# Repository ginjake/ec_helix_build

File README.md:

## LICENSE
creative commons non commercial

商用利用したい場合は twitter @sirojake にご相談ください  
please contact me for commercial use.
## developer 
ginjake

## 静電容量Helixとは？
Helix Keyboardの基板を差し替え、静電容量スイッチに対応させる為の基板です   
Varmiloスイッチ用とラバードーム用の2種類があり、別々の基板になっています。

## 外部の使用ライブラリ
### シンボルライブラリー
phi-kbd-library-master https://github.com/zk-phi/phi-kbd-library  
kbd https://github.com/foostan/kbd  

### フットプリントライブラリー
kbd https://github.com/foostan/kbd  
phi-kbd-library-master https://github.com/zk-phi/phi-kbd-library  
rd https://github.com/KiCad/kicad-footprints/tree/master/Resistor_SMD.pretty  
cs　https://github.com/KiCad/kicad-footprints/tree/master/Capacitor_SMD.pretty  

# 組み立て方 
本家Helixとの共通部分については省略しています。  
Varmilo版とラバードームで共通箇所が多いため、まとめて記載しています。

こちらのビルドログも参考になるので、目を通しておくと良いかもしれません  
https://orumin.blogspot.com/2020/10/helix-ec-helix-niz-ver.html

## 注意
本キットは組み立て難易度が高く、使うパーツも特殊です。  
自作キーボード初心者の方にはおすすめしません。  
通常のメカニカルスイッチでは動作せず、特殊なスイッチが必要になります。

# Varmiloスイッチについて
Varmilo社が出しているスイッチで、静電容量メカニカルとも呼ばれています。  
単体では販売されていないので、既製品を分解して入手する必要があります。  
ふもっふのお店のカスタムキーボードサービスで
デイジー軸 桜軸 ローズ軸などを選択して発注するのが一番手軽です。
https://jp.varmilo.com/keyboardproscenium/

# ラバードームスイッチについて
HHKBやREAL FORCE、NiZで採用されている方式です。  
トップハウジング、ステム、ラバードーム、コニックリングで構成されており、  
NiZキーボードを購入して分解することで全て手に入れることが出来ます。

## 部品

下記は両手分を作るのに必要なパーツ数です  

### 本家 Varmilo ラバードーム共通部品
| 名前 | 数 | 備考 |
| ---- | ---- | --- |
| Pro Micro | 2個 | |
| TRRSジャック | 2個 | |
| タクトスイッチ | 2個 | |
| スプリングピンヘッダ 12P | 4個 | コンスルーとも呼ばれています |
| プレート | 2セット| 遊舎工房の切り出しサービスがおすすめです|
| OLED保護プレート | 2枚 | |
| ゴム足 | 12個 |  |
| キーキャップ | 64個 | CherryMX軸 |
| 3.5mmオーディオケーブル | 左右合わせて1本 | 左右のキーボード接続用 |
| micro USBケーブル | 左右あわせて1本 | 
| OLEDモジュール | 2個 | OLED用（オプション） |
| ピンソケット 4P | 2個 | OLED用（オプション） |
| ピンヘッダ 4P | 2個 | OLED用（オプション） |
| M2スペーサー 8mm | 4個 | (OLED用)|
| sk6812mini| varmilo版 64個,ラバードーム版 54個  | LEDを付ける場合のみ|

### ラバードーム版追加部品
| 名前 | 数 | 備考 |
| ---- | ---- | --- |
| M5スペーサー | 8個 | |
| M2用ワッシャ | 8個(適宜) | |
| M2スペーサー 7mm| 8個 | |
| M2ネジ 4mm| 16個 | (低頭のほうが望ましい)|
| M2ネジ 6mm| 8個 | (低頭のほうが望ましい)|

### 本家と異なる部品
| 名前 | 数 | 備考 | 入手先 |
| ---- | ---- | --- | ---- |
| PCB | 2枚 | | |
| 静電容量キースイッチ | 64個 | 詳しくは後述します | |
| スイッチソケット | 64個 | varmilo版のみ https://yushakobo.jp/shop/a01ps/ | |
| 1608(0603)チップ抵抗 100K | 14 | | https://www.sengoku.co.jp/mod/sgk_cart/detail.php?code=EEHD-57HD |
| 1608(0603)チップ抵抗 10K | 4 | | https://www.sengoku.co.jp/mod/sgk_cart/detail.php?code=EEHD-57GX |
| 1608(0603)チップ抵抗 1KΩ | 4| | https://www.sengoku.co.jp/mod/sgk_cart/detail.php?code=EEHD-57GK |
| 1608(0603)チップ抵抗 200Ω | 12 | | https://www.sengoku.co.jp/mod/sgk_cart/detail.php?code=EEHD-57FZ |
| 1608(0603)チップ抵抗 51KΩ | 2 | | https://www.sengoku.co.jp/mod/sgk_cart/detail.php?code=EEHD-57H7 |
| 1608チップ積層セラミックコンデンサー 50Vdc 220pF | 2 | GRM1882C1H221JA01D*A (10個入り)| https://www.marutsu.co.jp/GoodsDetail.jsp?salesGoodsCode=19297&shopNo=3 |
|チップトランジスタ　2SC2712-GR 50V150m | 2 | | http://akizukidenshi.com/catalog/g/gI-00761/ |
| 74HC4051DB IC MUX/DEMUX 8X1 16SSOP | 2 | | https://www.marutsu.co.jp/pc/i/24340308/ |
| 2回路入オペアンプAD8616ARM | 2 | | http://akizukidenshi.com/catalog/g/gI-04570/ |
| ジャンパ用の銅線 | 少し | | |

### Varmilo版用キースイッチ
対応スイッチはVarmiloのECスイッチのみです。  
V1でもV2でも動作します。  

### Niz版用キースイッチ
メカニカルスイッチと異なり、複数のパーツが組み合わさって機能します。

| 名前  | 主な入手先 |
| ----  | ---- |
| 軸＆ハウジング  | https://www.nizkeyboard.com/collections/ornaments/products/2019-new-niz-ec-switch |
| ラバードーム  |  https://www.keyclack.com/products/bke-topre-dome-replacements?_pos=2&_sid=6025d869e&_ss=r もしくはREAL FORCEやNiz、HHKBから解体 |
| コニックリング | REAL FORCEやNiz、HHKB等から解体、もしくは https://btoshop.jp/2020/09/25/adelcps/ |

### ビットトレード版のスイッチについて
コニックリングとラバードームのみ対応しています。  
外形がcherryMXの企画と比べて若干大きいため、プレートが割れるなどの可能性があります。  
(アクリルカットサービスのモノは入りましたが、初期版のモノでは割れてしまいました。)  
ワッシャーが入らない等の問題もあるのでハウジングは使わず、コニックリングの回収に留めておくのが無難かもしれません。 
スペーサーやネジ、プレートを調整すれば使えるとは思います。  

## 追加で必要な工具
| 名前 | 数 | 備考 | 入手先 |
| ---- | ---- | --- | ---- |
| 絶縁テープ | 1つ | | |
| フラックス | 1つ | | |
| 拡大用ルーペ | 1つ | | |
| 懐中電灯 | 1つ | | |

## 組み立て方
右手用と左手用で若干異なります。  
写真は基本的にVarmilo版ですが、ラバードーム版でもほぼ同じです。    
ラバードーム版とVarmilo版はスイッチ部分のフットプリントが異なるだけです。   

__一度全ての工程を読み、理解してから作業を進めることをお勧めします。__

OLED,TRRSジャック等のHelixの共通部分については省略します。  
LEDについてはbacklightのみの対応です。  
(Varmilo版とラバードーム版で数が異なります)

## 絶縁テープとジャンパ(左手側のみ)
将来的にProMicroが刺さるところに絶縁テープを貼ります  

絶縁テープの上から、写真のようにジャンパしていきます。
この作業は左手側のみで、右手は不要です。   

ジャンパが完了したら、その上からさらに絶縁テープを貼った方が安心です。

また、絶縁テープを貼らず、ProMicro側を表裏逆転させる方法もありますが  
OLED用のスペーサーの高さが変わってしまうのであまりおすすめしません。

## その他のパーツを実装する
基板に書いてある通りにパーツを実装します。

74HC4051DB　と オペアンプAD8616ARMの向きには注意してください。  
チップ側の黒い丸上の凹みと、基板上のコの時のシルクが合わさるように置くのが正解です。  
隣のピンとショートしていないか、懐中電灯で照らしながらルーペで確認しておくのがおすすめです。

## リセットスイッチ
本家と同じです。

## スイッチソケットをつける(Varmilo版)
Varmilo版の場合、全てのキーにスイッチソケットをつけていきます。

## OLEDをつける(オプション)
本家と同じです

## TRRSジャックをつける
両手分つくる場合は必要になります。  
本家と同じです

## ProMicro
本家と同じです。

## ProMicroにqmkを焼く
下記のファームウェアを焼く必要があります。  
現在はNiz版とVarmilo版は同じファームになっています。   
https://github.com/ginjake/qmk_firmware/tree/ec_helix_niz   
``make ec_helix:test:avrdude`` もしくは 
``make ec_helix:ginjake:avrdude`` 

## トッププレート Varmilo版
トッププレートとスペーサーをネジ(短い方)で固定したら、向きに注意してスイッチを埋めていきます。

## トッププレート ラバードーム版
トッププレートにワッシャとスペーサーをネジ(短い方)で固定してから、スイッチをアクリルに差込みます。  
ワッシャはスペーサー1つに対して1枚が基本ですが、ネジやスペーサーの長さ、アクリルの太さによって変化します。
このあたりは適宜調整してください。
ネジ→トッププレート→ワッシャ→スペーサー　のような順番になるように固定しましょう。  
中に軸を入れてラバードームでフタをします。  
スペーサーとラバードームが干渉しないよう、ハサミで切りましょう  
ラバードームの凹みの中にコニックリングを入れます。  

このとき、コニックリングが重ね合っていないか気を付けましょう。  
複数個が重なっていても意外と気付かず、誤作動の原因になります。  

## ボトムプレート(ラバードーム版)
基板とボトムプレートの間にM5スペーサーが入るようにネジ止め(長い方)しましょう。  
Varmilo版は普通にネジで止めてしまって大丈夫です。

## 完成

## qmkコンパイル時の諸注意
・OLEDをつけない場合は `rule.mk` の `OLED_DRIVER_ENABLE` を `no` にしてください。 
無駄な負荷がかかり、取りこぼしが発生する可能性が高くなります。   
・Varmilo版とラバードーム版でledの数が異なります。 `config.h` の `RGBLED_NUM` の数を適宜変更してください

・ステンレスプレートを使う場合は　`config.h` の `#define STAINLESS_PLATE` のコメントアウトを外してください。ステンレスプレートは実験的な対応の為、動作保証対象外となります。

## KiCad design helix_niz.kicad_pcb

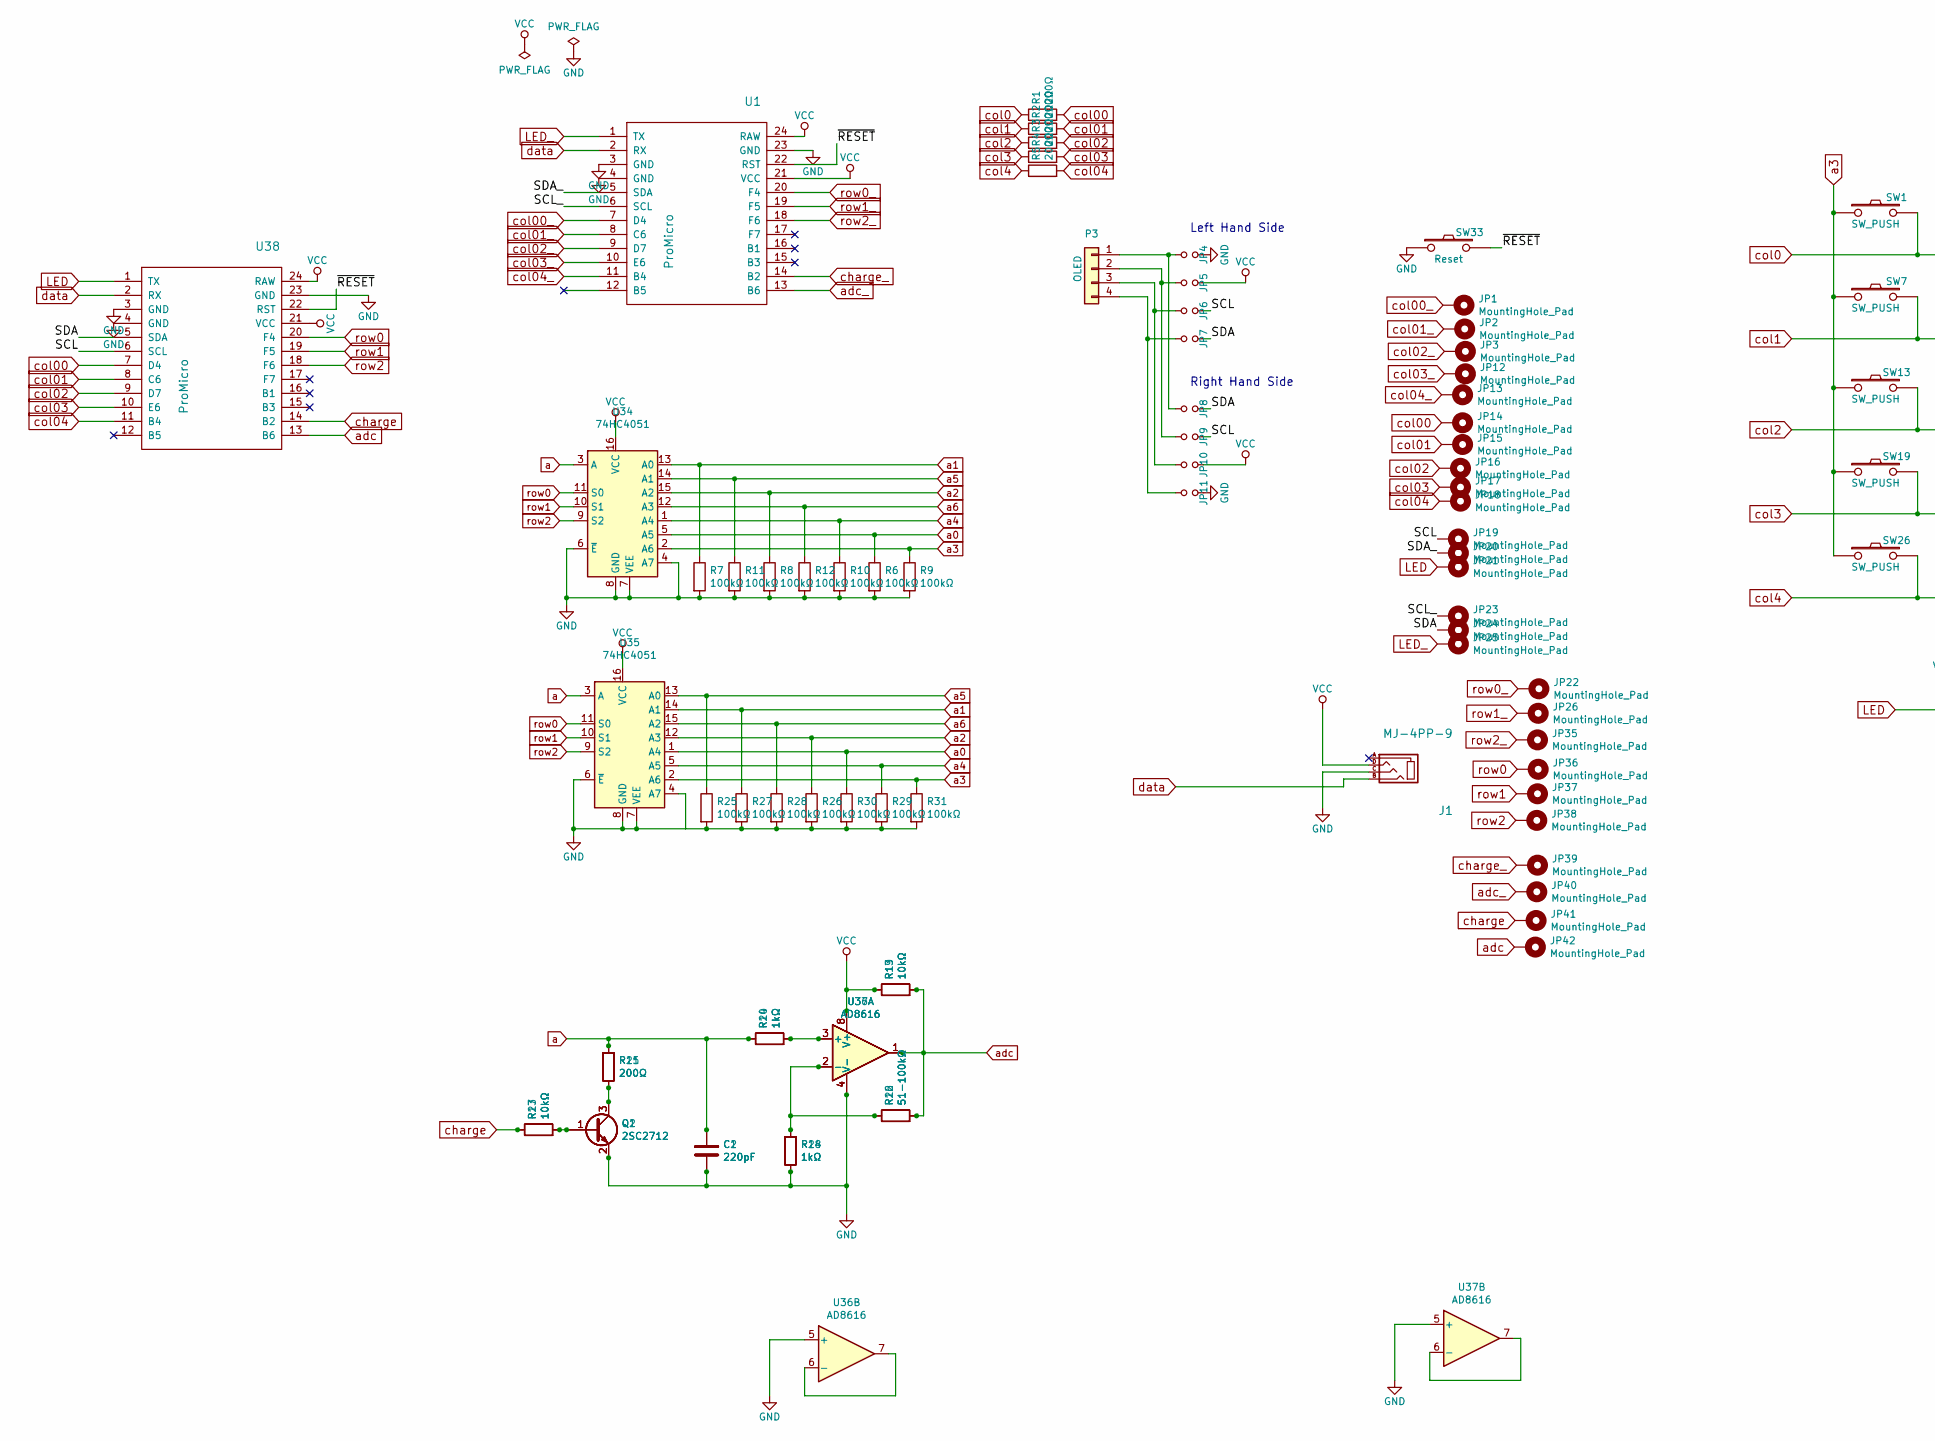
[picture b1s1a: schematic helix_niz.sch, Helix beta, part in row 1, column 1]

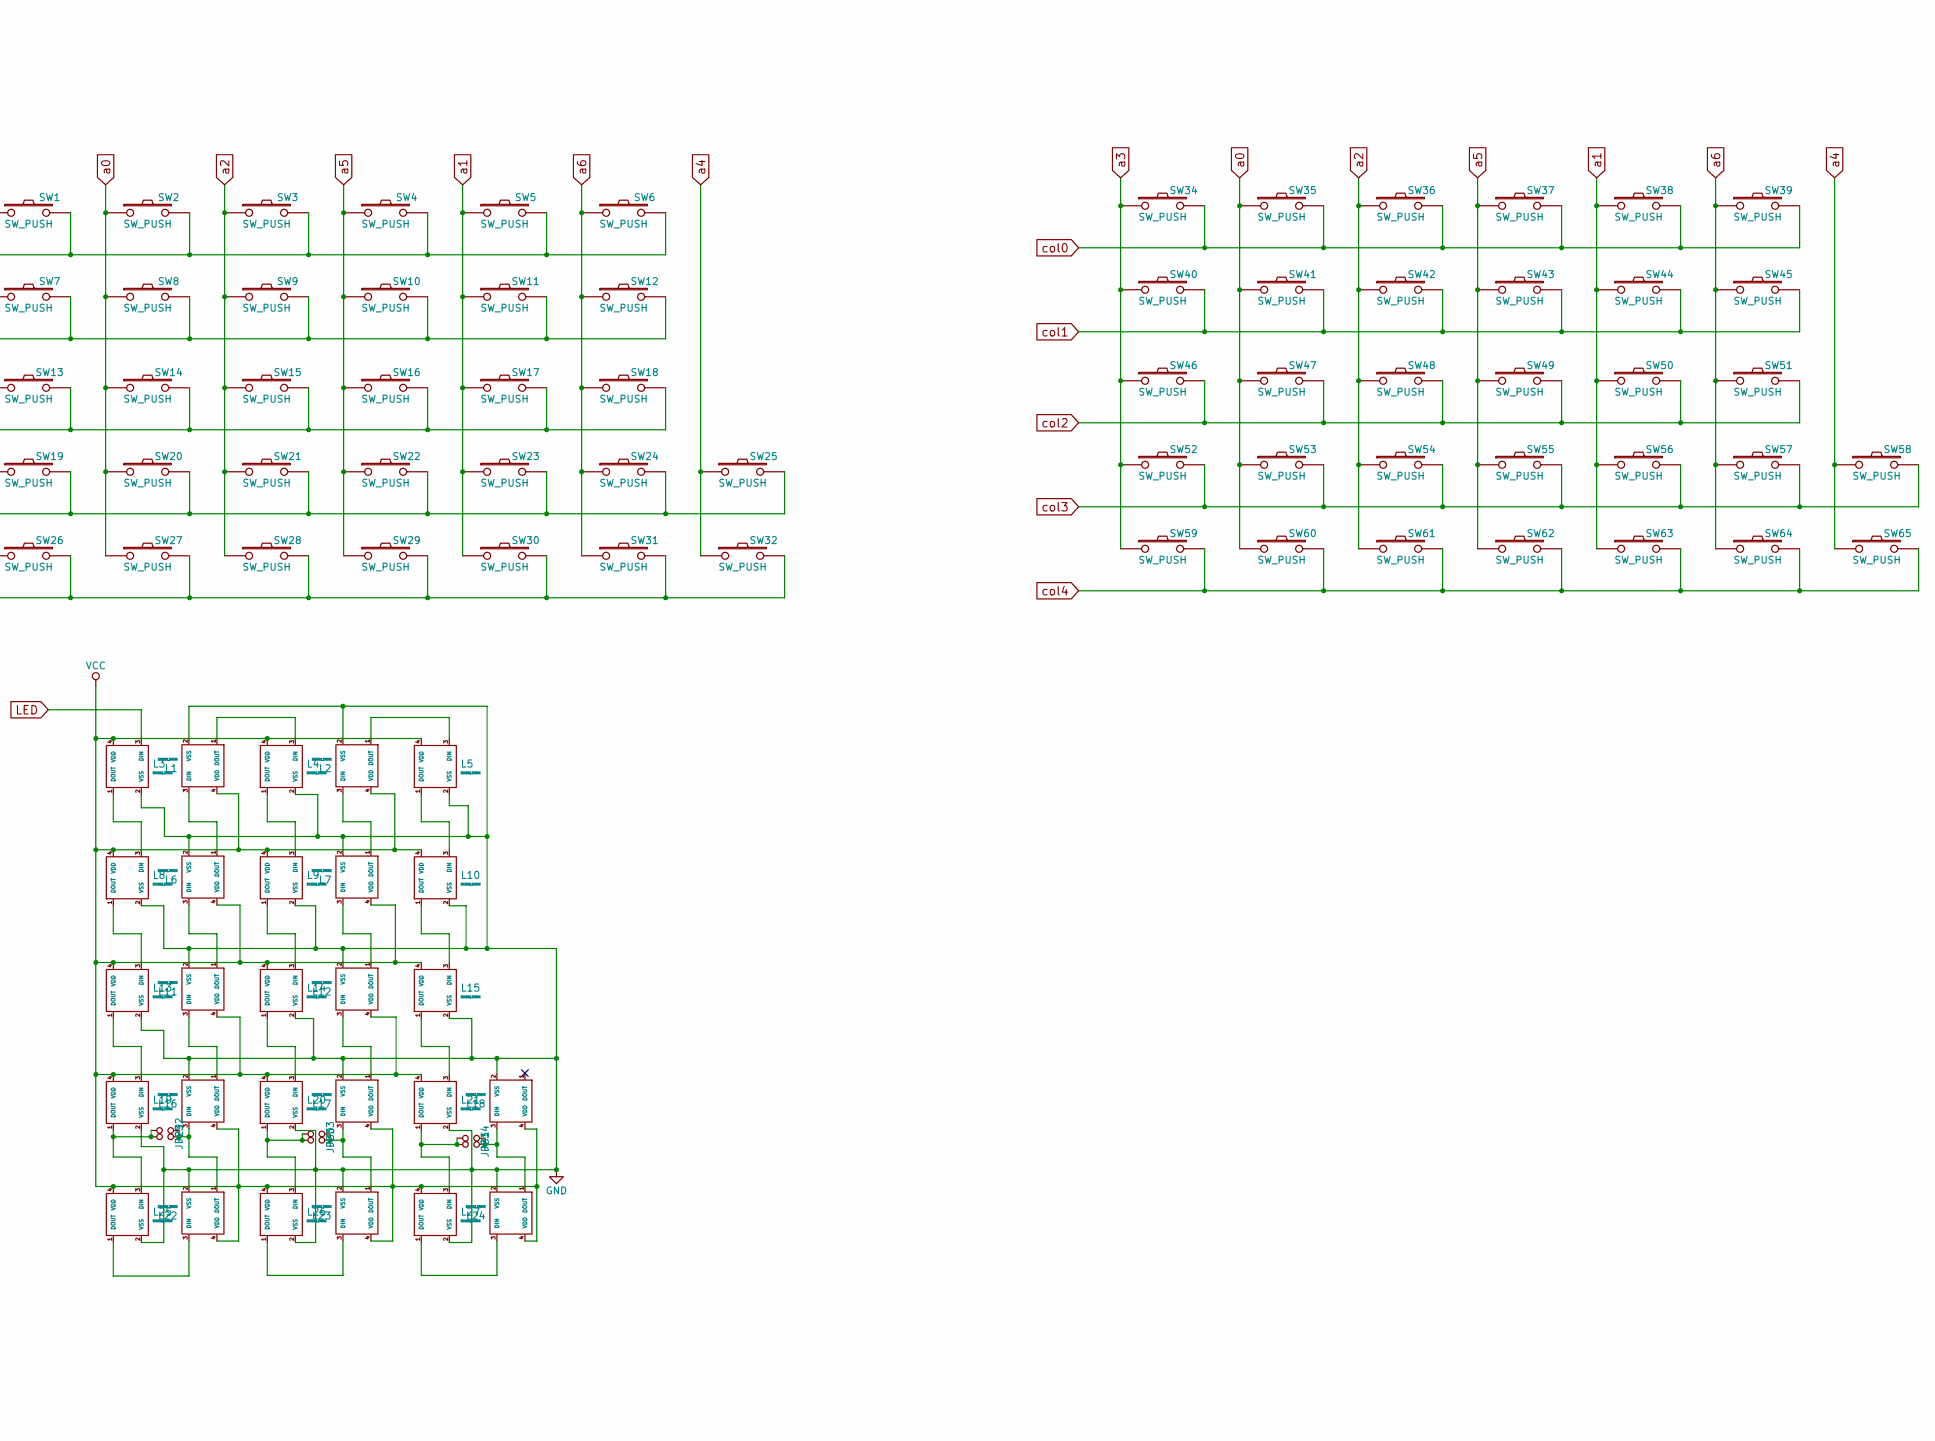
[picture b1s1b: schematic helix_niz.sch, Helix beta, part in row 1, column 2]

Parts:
C1, C2: 220pF; C_0603_1608Metric
J1: MJ-4PP-9
JP1, JP2, JP3, JP12, JP13, JP14, JP15, JP16, JP17, JP18, JP19, JP20, JP21, JP22, JP23, JP24, JP25, JP26, JP35, JP36, JP37, JP38, JP39, JP40, JP41, JP42: MountingHole_Pad; THSmallest
JP4, JP11, JP29, JP30, JP31, JP32, JP33, JP34: GND; Jumper
JP5, JP10: VCC; Jumper
JP6, JP9: SCL; Jumper
JP7, JP8: SDA; Jumper
L1, L2, L3, L4, L5, L6, L7, L8, L9, L10, L11, L12, L13, L14, L15, L16, L17, L18, L19, L20, L21, L22, L23, L24, L25, L26, L27: SK6812MINI; SK6812MINI_rev
P3: OLED
Q1, Q2: 2SC2712
R1, R2, R3, R4, R5, R15, R21: 200Ω; R_0603_1608Metric
R6, R7, R8, R9, R10, R11, R12, R25, R26, R27, R28, R29, R30, R31: 100kΩ; R_0603_1608Metric
R13, R17, R19, R23: 10kΩ; R_0603_1608Metric
R14, R18, R20, R24: 1kΩ; R_0603_1608Metric
R16, R22: 51-100kΩ; R_0603_1608Metric
SW1, SW2, SW3, SW4, SW5, SW6, SW7, SW8, SW9, SW10, SW11, SW12, SW13, SW14, SW15, SW16, SW17, SW18, SW19, SW20, SW21, SW22, SW23, SW24, SW25, SW26, SW27, SW28, SW29, SW30, SW31, SW32, SW34, SW35, SW36, SW37, SW38, SW39, SW40, SW41, SW42, SW43, SW44, SW45, SW46, SW47, SW48, SW49, SW50, SW51, SW52, SW53, SW54, SW55, SW56, SW57, SW58, SW59, SW60, SW61, SW62, SW63, SW64, SW65: SW_PUSH; niz
SW33: Reset; ResetSW
U1, U38: ProMicro; ProMicro_v3.5
U34, U35: 74HC4051; SSOP16
U36, U37: AD8616

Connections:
/SCL: JP6.2, JP9.2, JP19.1, U38.6 (SCL)
/SCL_: JP23.1, U1.6 (SCL)
/SDA: JP7.2, JP8.2, JP24.1, U38.5 (SDA)
/SDA_: JP20.1, U1.5 (SDA)
/~RESET: SW33.2, U1.22 (RST), U38.22 (RST)
GND: C1.2, C2.2, J1.C, JP4.2, JP11.2, L1.2 (VSS), L2.2 (VSS), L3.2 (VSS), L4.2 (VSS), L5.2 (VSS), L6.2 (VSS), L7.2 (VSS), L8.2 (VSS), L9.2 (VSS), L10.2 (VSS), L11.2 (VSS), L12.2 (VSS), L13.2 (VSS), L14.2 (VSS), L15.2 (VSS), L16.2 (VSS), L17.2 (VSS), L18.2 (VSS), L19.2 (VSS), L20.2 (VSS), L21.2 (VSS), L22.2 (VSS), L23.2 (VSS), L24.2 (VSS), L25.2 (VSS), L26.2 (VSS), L27.2 (VSS), Q1.2 (E), Q2.2 (E), R6.2, R7.2, R8.2, R9.2, R10.2, R11.2, R12.2, R18.2, R24.2, R25.2, R26.2, R27.2, R28.2, R29.2, R30.2, R31.2, SW33.1, U1.3 (GND), U1.4 (GND), U1.23 (GND), U34.4 (A7), U34.6 (~E), U34.7 (VEE), U34.8 (GND), U35.4 (A7), U35.6 (~E), U35.7 (VEE), U35.8 (GND), U36.4 (V-), U36.5 (+), U37.4 (V-), U37.5 (+), U38.3 (GND), U38.4 (GND), U38.23 (GND)
LED: JP21.1, L3.3 (DIN), U38.1 (TX)
LED_: JP25.1, U1.1 (TX)
unnamed: JP4.1, JP8.1, P3.1
unnamed: JP5.1, JP9.1, P3.2
unnamed: JP6.1, JP10.1, P3.3
unnamed: JP7.1, JP11.1, P3.4
unnamed: JP29.1, JP32.1, L19.1 (DOUT), L25.3 (DIN)
unnamed: JP29.2, JP32.2, L16.3 (DIN), L22.1 (DOUT)
unnamed: JP30.1, JP33.1, L20.1 (DOUT), L26.3 (DIN)
unnamed: JP30.2, JP33.2, L17.3 (DIN), L23.1 (DOUT)
unnamed: JP31.1, JP34.1, L21.1 (DOUT), L27.3 (DIN)
unnamed: JP31.2, JP34.2, L18.3 (DIN), L24.1 (DOUT)
unnamed: L1.1 (DOUT), L4.3 (DIN)
unnamed: L1.3 (DIN), L6.1 (DOUT)
unnamed: L2.1 (DOUT), L5.3 (DIN)
unnamed: L2.3 (DIN), L7.1 (DOUT)
unnamed: L3.1 (DOUT), L8.3 (DIN)
unnamed: L4.1 (DOUT), L9.3 (DIN)
unnamed: L10.1 (DOUT), L15.3 (DIN)
unnamed: L5.1 (DOUT), L10.3 (DIN)
unnamed: L6.3 (DIN), L11.1 (DOUT)
unnamed: L11.3 (DIN), L16.1 (DOUT)
unnamed: L7.3 (DIN), L12.1 (DOUT)
unnamed: L12.3 (DIN), L17.1 (DOUT)
unnamed: L13.1 (DOUT), L19.3 (DIN)
unnamed: L8.1 (DOUT), L13.3 (DIN)
unnamed: L14.1 (DOUT), L20.3 (DIN)
unnamed: L9.1 (DOUT), L14.3 (DIN)
unnamed: L15.1 (DOUT), L21.3 (DIN)
unnamed: L22.3 (DIN), L25.1 (DOUT)
unnamed: L23.3 (DIN), L26.1 (DOUT)
unnamed: L24.3 (DIN), L27.1 (DOUT)
unnamed: Q1.1 (B), Q2.1 (B), R17.2, R23.2
unnamed: Q1.3 (C), Q2.3 (C), R15.2, R21.2
unnamed: R14.2, R20.2, U36.3 (+), U37.3 (+)
unnamed: R16.1, R18.1, R22.1, R24.1, U36.2 (-), U37.2 (-)
unnamed: U36.6 (-), U36.7
unnamed: U37.6 (-), U37.7
VCC: J1.D, JP5.2, JP10.2, L1.4 (VDD), L2.4 (VDD), L3.4 (VDD), L4.4 (VDD), L5.4 (VDD), L6.4 (VDD), L7.4 (VDD), L8.4 (VDD), L9.4 (VDD), L10.4 (VDD), L11.4 (VDD), L12.4 (VDD), L13.4 (VDD), L14.4 (VDD), L15.4 (VDD), L16.4 (VDD), L17.4 (VDD), L18.4 (VDD), L19.4 (VDD), L20.4 (VDD), L21.4 (VDD), L22.4 (VDD), L23.4 (VDD), L24.4 (VDD), L25.4 (VDD), L26.4 (VDD), L27.4 (VDD), R13.1, R19.1, U1.21 (VCC), U1.24 (RAW), U34.16 (VCC), U35.16 (VCC), U36.8 (V+), U37.8 (V+), U38.21 (VCC), U38.24 (RAW)
a: C1.1, C2.1, R14.1, R15.1, R20.1, R21.1, U34.3 (A), U35.3 (A)
a0: R6.1, R30.1, SW2.1, SW8.1, SW14.1, SW20.1, SW27.1, SW35.1, SW41.1, SW47.1, SW53.1, SW60.1, U34.5 (A5), U35.1 (A4)
a1: R7.1, R27.1, SW5.1, SW11.1, SW17.1, SW23.1, SW30.1, SW38.1, SW44.1, SW50.1, SW56.1, SW63.1, U34.13 (A0), U35.14 (A1)
a2: R8.1, R26.1, SW3.1, SW9.1, SW15.1, SW21.1, SW28.1, SW36.1, SW42.1, SW48.1, SW54.1, SW61.1, U34.15 (A2), U35.12 (A3)
a3: R9.1, R31.1, SW1.1, SW7.1, SW13.1, SW19.1, SW26.1, SW34.1, SW40.1, SW46.1, SW52.1, SW59.1, U34.2 (A6), U35.2 (A6)
a4: R10.1, R29.1, SW25.1, SW32.1, SW58.1, SW65.1, U34.1 (A4), U35.5 (A5)
a5: R11.1, R25.1, SW4.1, SW10.1, SW16.1, SW22.1, SW29.1, SW37.1, SW43.1, SW49.1, SW55.1, SW62.1, U34.14 (A1), U35.13 (A0)
a6: R12.1, R28.1, SW6.1, SW12.1, SW18.1, SW24.1, SW31.1, SW39.1, SW45.1, SW51.1, SW57.1, SW64.1, U34.12 (A3), U35.15 (A2)
adc: JP42.1, R13.2, R16.2, R19.2, R22.2, U36.1, U37.1, U38.13 (B6)
adc_: JP40.1, U1.13 (B6)
charge: JP41.1, R17.1, R23.1, U38.14 (B2)
charge_: JP39.1, U1.14 (B2)
col0: R1.1, SW1.2, SW2.2, SW3.2, SW4.2, SW5.2, SW6.2, SW34.2, SW35.2, SW36.2, SW37.2, SW38.2, SW39.2; also elsewhere on the board
col00: JP14.1, R1.2, U38.7 (D4); also elsewhere on the board
col00_: JP1.1, U1.7 (D4)
col1: R2.1, SW7.2, SW8.2, SW9.2, SW10.2, SW11.2, SW12.2, SW40.2, SW41.2, SW42.2, SW43.2, SW44.2, SW45.2; also elsewhere on the board
col01: JP15.1, R2.2, U38.8 (C6); also elsewhere on the board
col01_: JP2.1, U1.8 (C6)
col2: R3.1, SW13.2, SW14.2, SW15.2, SW16.2, SW17.2, SW18.2, SW46.2, SW47.2, SW48.2, SW49.2, SW50.2, SW51.2; also elsewhere on the board
col02: JP16.1, R3.2, U38.9 (D7); also elsewhere on the board
col02_: JP3.1, U1.9 (D7)
col3: R4.1, SW19.2, SW20.2, SW21.2, SW22.2, SW23.2, SW24.2, SW25.2, SW52.2, SW53.2, SW54.2, SW55.2, SW56.2, SW57.2, SW58.2; also elsewhere on the board
col03: JP17.1, R4.2, U38.10 (E6); also elsewhere on the board
col03_: JP12.1, U1.10 (E6)
col4: R5.1, SW26.2, SW27.2, SW28.2, SW29.2, SW30.2, SW31.2, SW32.2, SW59.2, SW60.2, SW61.2, SW62.2, SW63.2, SW64.2, SW65.2; also elsewhere on the board
col04: JP18.1, R5.2, U38.11 (B4); also elsewhere on the board
col04_: JP13.1, U1.11 (B4)
data: J1.B, U1.2 (RX), U38.2 (RX)
row0: JP36.1, U34.11 (S0), U35.11 (S0), U38.20 (F4)
row0_: JP22.1, U1.20 (F4)
row1: JP37.1, U34.10 (S1), U35.10 (S1), U38.19 (F5)
row1_: JP26.1, U1.19 (F5)
row2: JP38.1, U34.9 (S2), U35.9 (S2), U38.18 (F6)
row2_: JP35.1, U1.18 (F6)

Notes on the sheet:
Left Hand Side
Right Hand Side

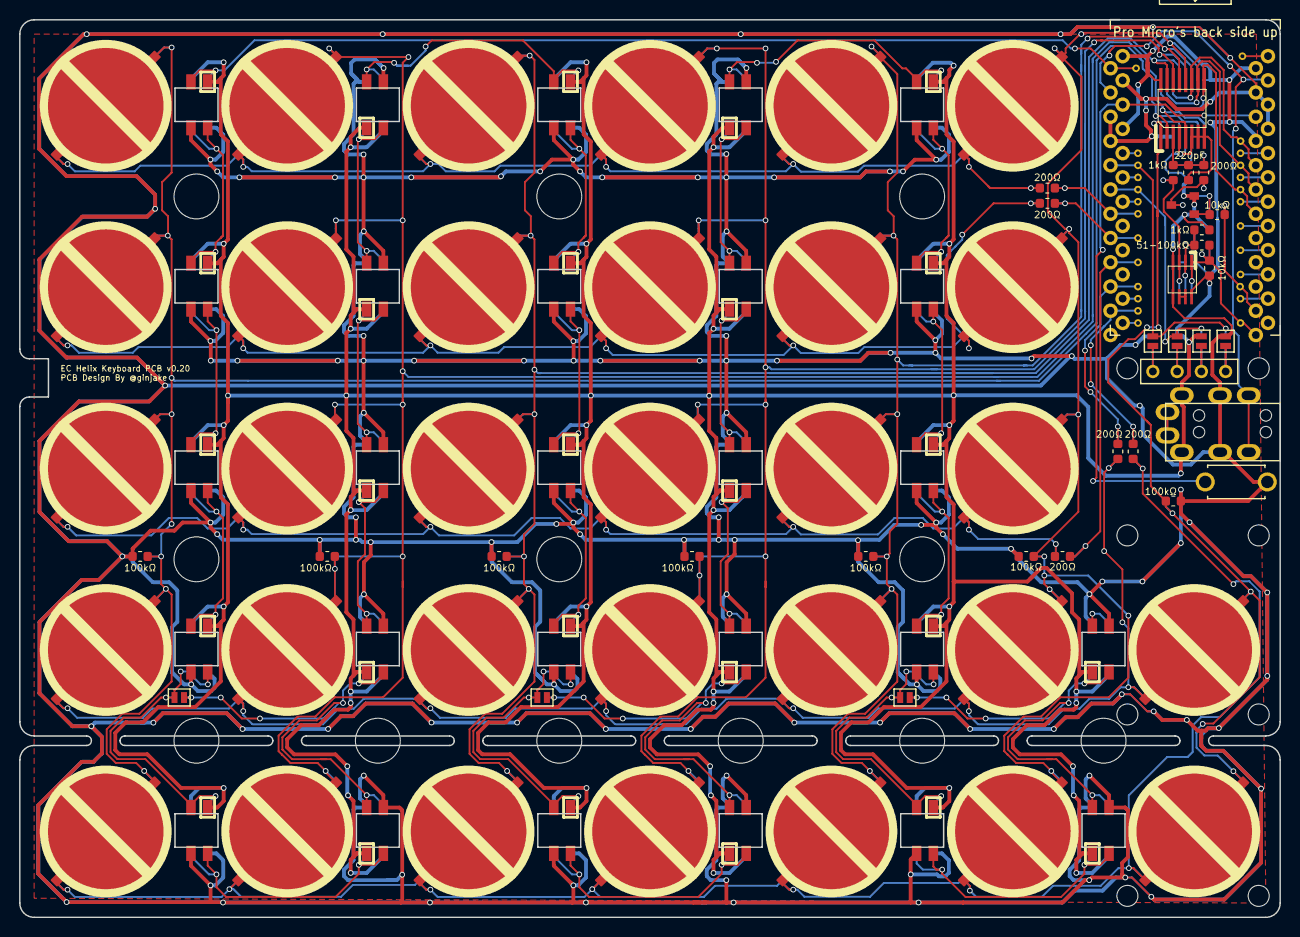
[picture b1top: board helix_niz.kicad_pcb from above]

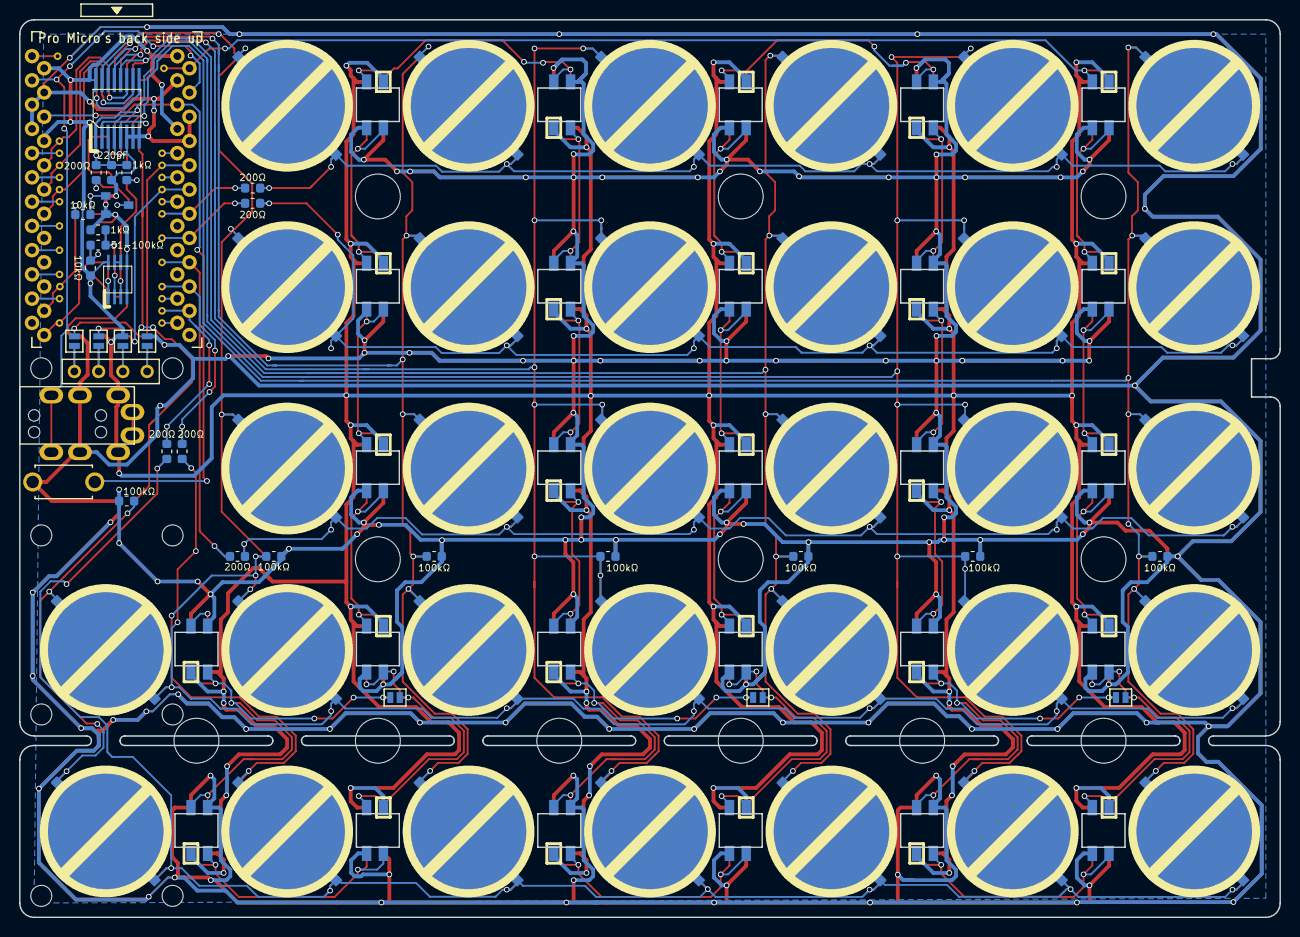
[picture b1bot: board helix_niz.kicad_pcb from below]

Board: 2 copper layers, 132.0 x 94.0 mm, 200 parts (62 on the bottom side), 79 nets.

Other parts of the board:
HOLE_3M, HOLE_3M#2, HOLE_3M#3, HOLE_3M#4, HOLE_3M#5, HOLE_3M#6, HOLE_3M#7, HOLE_3M#8, HOLE_3M#9, HOLE_3M#10, HOLE_3M#11, HOLE_3M#12: VAL**; HOLE_M2_TH
HOLE_M2, HOLE_M2#2, HOLE_M2#3, HOLE_M2#4, HOLE_M2#5, HOLE_M2#6, HOLE_M2#7, HOLE_M2#8: VAL**; HOLE_M2
R32, R33, R34, R35, R36: 200Ω; R_0603_1608Metric

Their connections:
col0: R32.1; also elsewhere on the board
col00: R32.2; also elsewhere on the board
col1: R33.1; also elsewhere on the board
col01: R33.2; also elsewhere on the board
col2: R34.1; also elsewhere on the board
col02: R34.2; also elsewhere on the board
col3: R35.1; also elsewhere on the board
col03: R35.2; also elsewhere on the board
col4: R36.1; also elsewhere on the board
col04: R36.2; also elsewhere on the board

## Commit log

2020-06-20 コミット
2020-08-19 ノイズ対策＆nizとvarmiloを同じリポジトリにした
2020-09-07 更新した
